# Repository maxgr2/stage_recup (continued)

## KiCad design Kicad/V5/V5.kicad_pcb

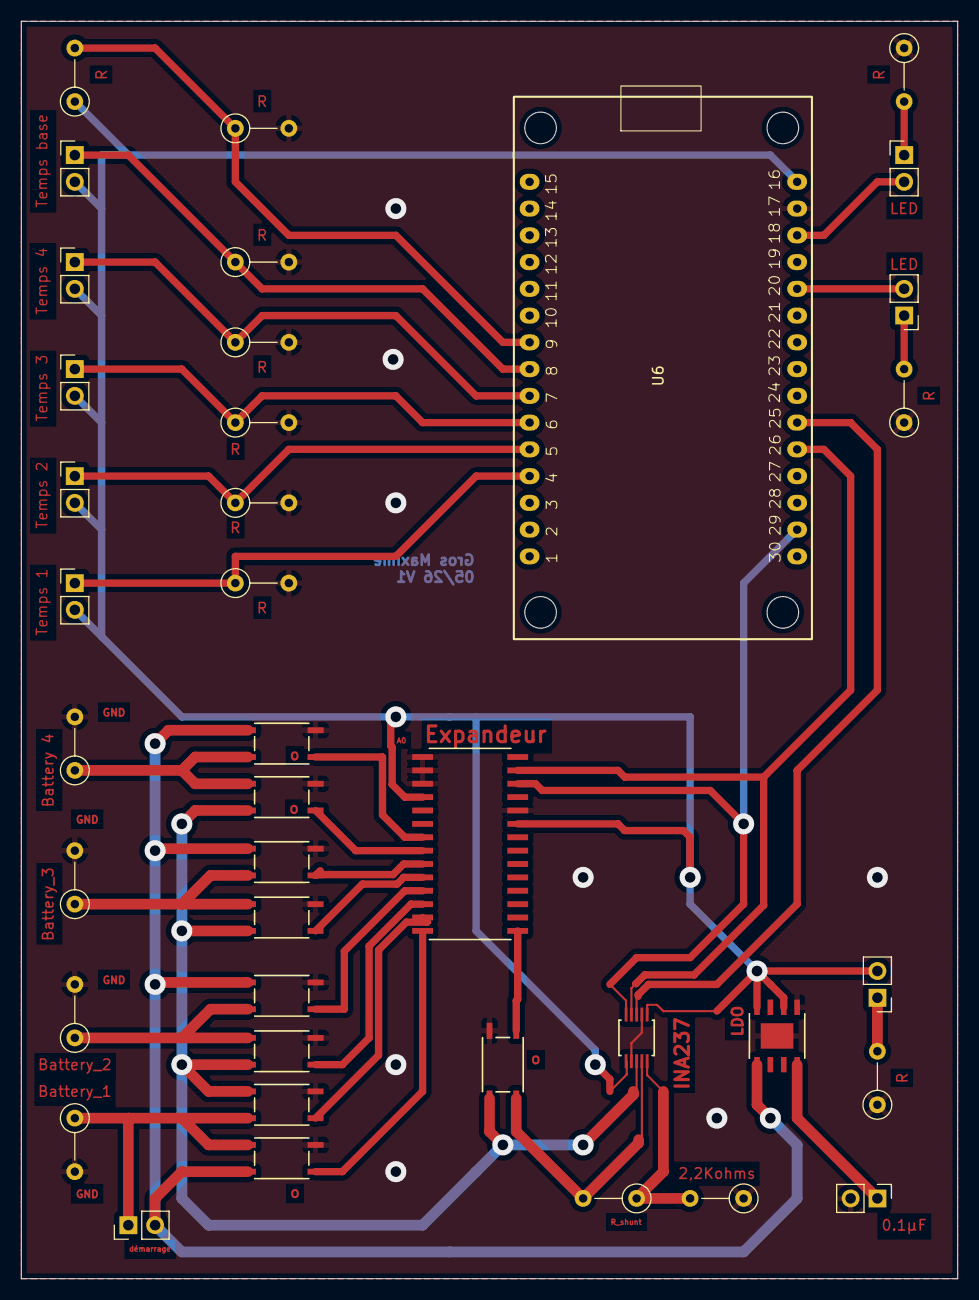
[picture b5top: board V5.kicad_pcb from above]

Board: 2 copper layers, 88.9 x 119.4 mm, 39 parts (0 on the bottom side), 34 nets.

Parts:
BT1: Battery_1; R_Axial_DIN0207_L6.3mm_D2.5mm_P5.08mm_Vertical
BT2: Battery_2; R_Axial_DIN0207_L6.3mm_D2.5mm_P5.08mm_Vertical
BT3: Battery_3; R_Axial_DIN0207_L6.3mm_D2.5mm_P5.08mm_Vertical
BT4: Battery 4; R_Axial_DIN0207_L6.3mm_D2.5mm_P5.08mm_Vertical
C1: 0.1µF; PinHeader_1x02_P2.54mm_Vertical
D1, D2, D3: LED; PinHeader_1x02_P2.54mm_Vertical
J1, J2, J3, J4, J5, J6: Conn_01x02_Pin; PinHeader_1x02_P2.54mm_Vertical
R1, R3, R4, R5, R6, R7, R8, R9, R10, R11, R12: R; R_Axial_DIN0207_L6.3mm_D2.5mm_P5.08mm_Vertical
R2: 2,2Kohms; R_Axial_DIN0207_L6.3mm_D2.5mm_P5.08mm_Vertical
U1, U2, U4, U8, U9, U10, U11, U12, U13: ISOM8600DFGR
U3: MCP23017-E/SO; MCP23017T-E&slash_SO
U5: MIC5283-3.3YME
U6: ESP32_30pin
U7: INA237AIDGSR

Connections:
+3.3V: D2.2 (A), J2.2, J3.2, J4.2, J5.2, J6.2, R5.1, U3.9 (VDD), U3.18 (*RESET), U5.6 (SNS), U5.8 (VOUT), U6.16 (3.3v), U7.1 (A1), U7.6 (VS)
CONT_ALIM1: U2.1 (AN), U3.28 (GPA7)
CONT_ALIM2: U3.25 (GPA4), U9.1 (AN)
CONT_ALIM3: U3.23 (GPA2), U11.1 (AN)
CONT_ALIM4: U3.21 (GPA0), U13.1 (AN)
CONT_MES1: U1.1 (AN), U3.27 (GPA6)
CONT_MES2: U3.26 (GPA5), U8.1 (AN)
CONT_MES3: U3.24 (GPA3), U10.1 (AN)
CONT_MES4: U3.22 (GPA1), U12.1 (AN)
GND: BT1.2 (-), BT2.2 (-), BT3.2 (-), BT4.2 (-), C1.2, R1.1, R2.1, R4.1, R6.2, R7.2, R8.2, R9.2, R10.2, R11.1, R12.2, U1.2 (CAT), U2.2 (CAT), U3.10 (VSS), U3.15 (A0), U3.16 (A1), U3.17 (A2), U4.2 (CAT), U5.5 (GND), U6.17 (GND), U7.2 (A0), U7.7 (GND), U8.2 (CAT), U9.2 (CAT), U10.2 (CAT), U11.2 (CAT), U12.2 (CAT), U13.2 (CAT)
MES_TOT: U3.1 (GPB0), U4.1 (AN)
unnamed: BT1.1 (+), J1.1, U1.4 (S1), U2.3 (S2)
unnamed: BT2.1 (+), U8.3 (S2), U9.4 (S1)
unnamed: BT3.1 (+), U10.3 (S2), U11.4 (S1)
unnamed: BT4.1 (+), U12.3 (S2), U13.4 (S1)
unnamed: D1.2 (A), U6.20 (GPIO4)
unnamed: D1.1 (K), R1.2
unnamed: D2.1 (K), R4.2
unnamed: D3.2 (A), U6.18 (GPIO15)
unnamed: D3.1 (K), R11.2
unnamed: R3.2, U4.4 (S1), U7.9 (IN-)
unnamed: C1.1, U5.4 (CPSRR)
unnamed: R2.2, R3.1, U7.10 (IN+)
SCL: U3.12 (SCL), U6.29 (GPIO22), U7.5 (SCL)
SDA: U3.13 (SDA), U6.26 (GPIO21), U7.4 (SDA)
VIN_LDO: J1.2, U2.4 (S1), U5.1 (VIN), U9.3 (S2), U11.3 (S2), U13.3 (S2)
V_BUS: U1.3 (S2), U4.3 (S2), U7.8 (VBUS), U8.4 (S1), U10.4 (S1), U12.4 (S1)
alert_INA237: U6.25 (GPIO19), U7.3 (ALERT)
temp_1: J2.1, R7.1, U6.7 (GPIO26)
temp_2: J3.1, R8.1, U6.6 (GPIO27)
temp_3: J4.1, R9.1, U6.5 (GPIO14)
temp_4: J5.1, R10.1, U6.4 (GPIO12)
temp_5: J6.1, R12.1, U6.8 (GPIO25)
temp_base: R5.2, R6.1, U6.9 (GPIO33)

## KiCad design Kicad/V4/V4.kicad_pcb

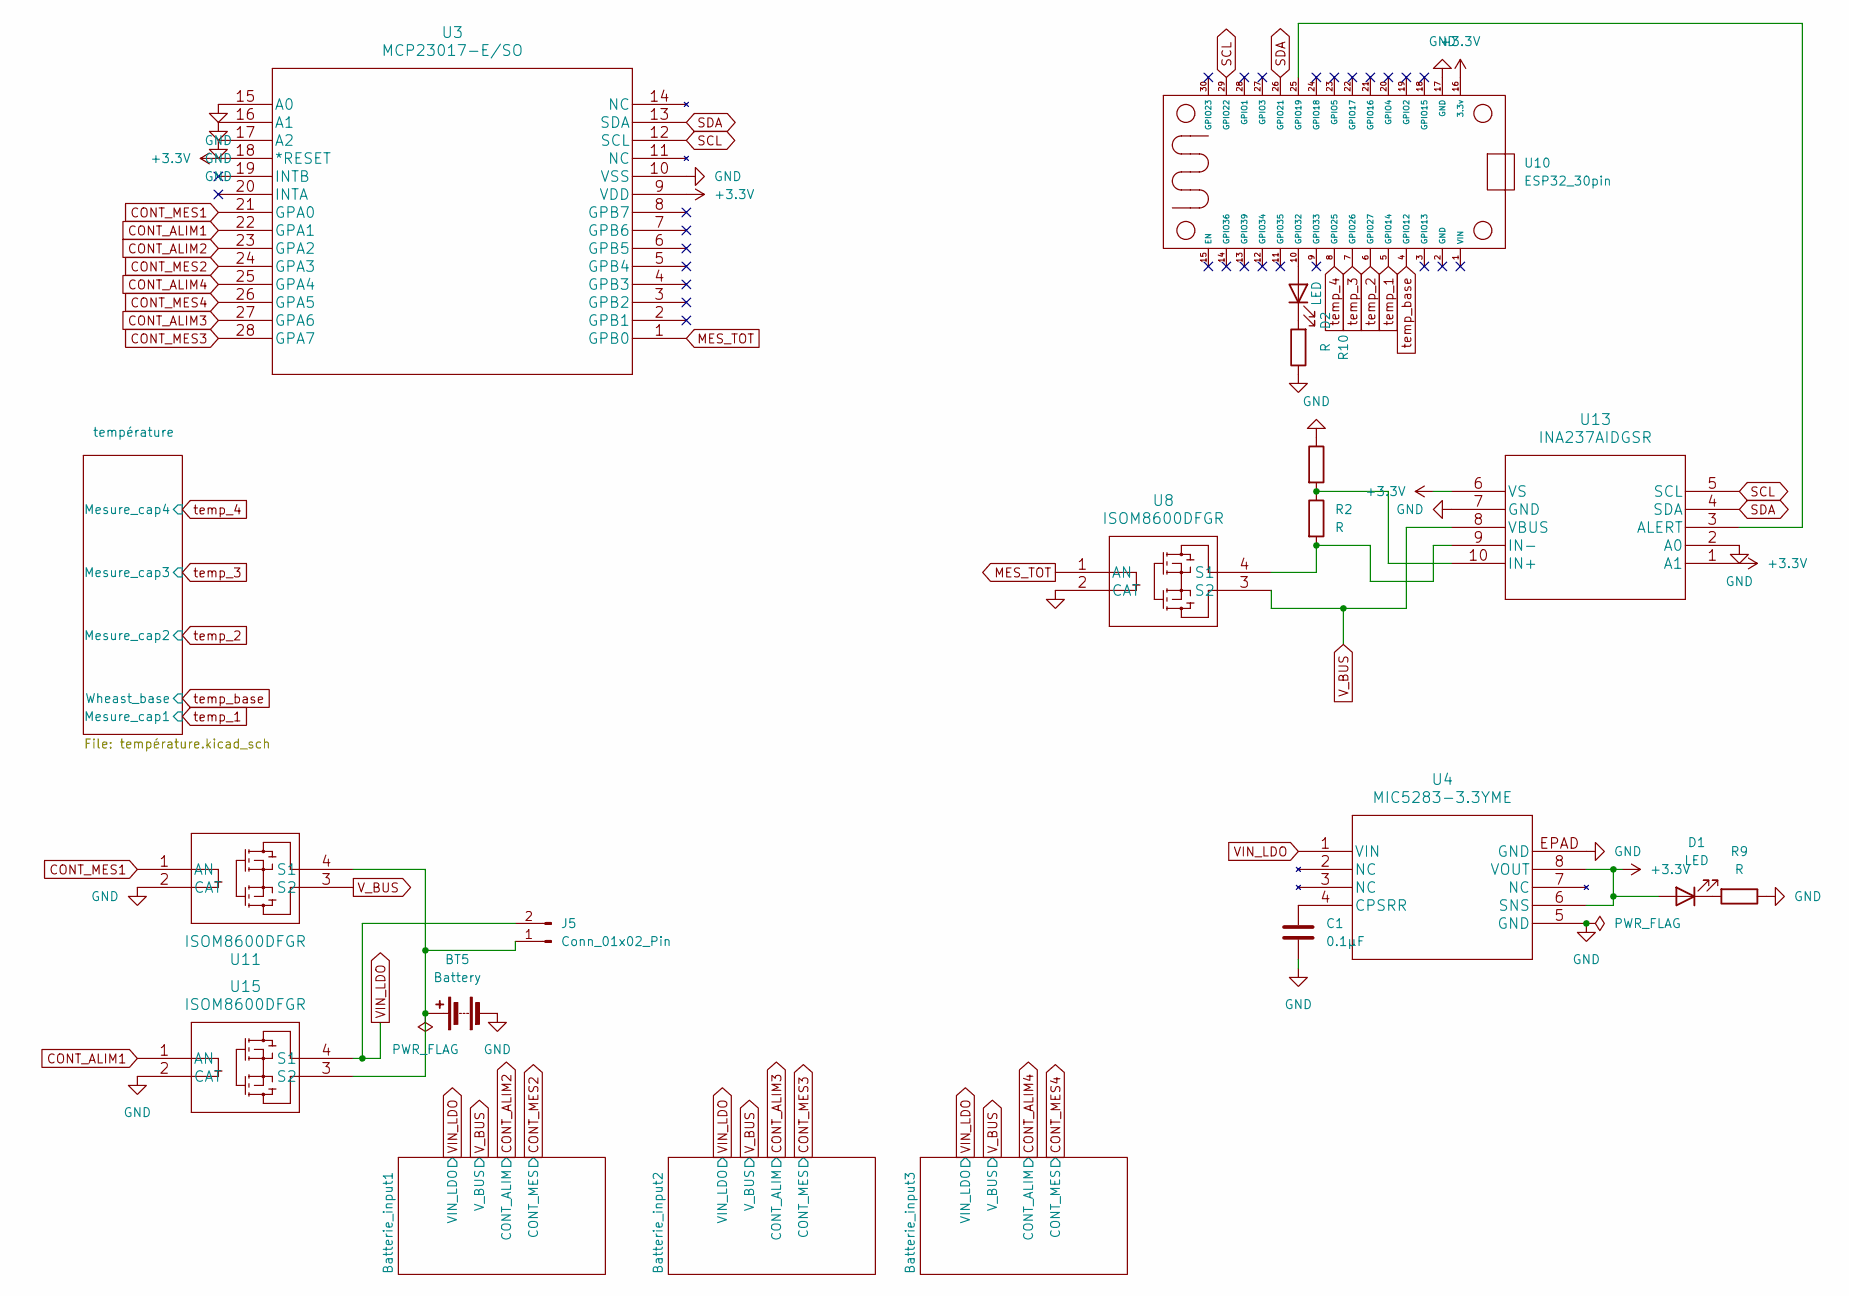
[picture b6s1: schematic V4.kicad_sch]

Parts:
BT5: Battery; PinHeader_1x02_P2.54mm_Vertical
C1: 0.1µF; PinHeader_1x02_P2.54mm_Vertical
D1, D2: LED; PinHeader_1x02_P2.54mm_Vertical
J5: Conn_01x02_Pin; PinHeader_1x02_P2.54mm_Vertical
R1: 2,2Kohms; R_Axial_DIN0207_L6.3mm_D2.5mm_P5.08mm_Vertical
R2, R9, R10: R; R_Axial_DIN0207_L6.3mm_D2.5mm_P5.08mm_Vertical
U3: MCP23017-E/SO; MCP23017T-E&slash_SO
U4: MIC5283-3.3YME
U8, U11, U15: ISOM8600DFGR
U10: ESP32_30pin
U13: INA237AIDGSR

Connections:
+3.3V: D1.2 (A), U3.9 (VDD), U3.18 (*RESET), U4.6 (SNS), U4.8 (VOUT), U10.16 (3.3v), U13.1 (A1), U13.6 (VS); also elsewhere on the board
CONT_ALIM1: U3.22 (GPA1), U15.1 (AN)
CONT_ALIM2: U3.23 (GPA2); also elsewhere on the board
CONT_ALIM3: U3.27 (GPA6); also elsewhere on the board
CONT_ALIM4: U3.25 (GPA4); also elsewhere on the board
CONT_MES1: U3.21 (GPA0), U11.1 (AN)
CONT_MES2: U3.24 (GPA3); also elsewhere on the board
CONT_MES3: U3.28 (GPA7); also elsewhere on the board
CONT_MES4: U3.26 (GPA5); also elsewhere on the board
GND: BT5.2 (-), C1.2, R1.1, R9.1, R10.1, U3.10 (VSS), U3.15 (A0), U3.16 (A1), U3.17 (A2), U4.5 (GND), U4.EPAD (GND), U8.2 (CAT), U10.17 (GND), U11.2 (CAT), U13.2 (A0), U13.7 (GND), U15.2 (CAT); also elsewhere on the board
MES_TOT: U3.1 (GPB0), U8.1 (AN)
unnamed: BT5.1 (+), J5.1, U11.4 (S1), U15.3 (S2)
unnamed: D1.1 (K), R9.2
unnamed: D2.2 (A), U10.10 (GPIO32)
unnamed: D2.1 (K), R10.2
unnamed: C1.1, U4.4 (CPSRR)
unnamed: U10.25 (GPIO19), U13.3 (ALERT)
unnamed: R1.2, R2.1, U13.10 (IN+)
unnamed: R2.2, U8.4 (S1), U13.9 (IN-)
SCL: U3.12 (SCL), U10.29 (GPIO22), U13.5 (SCL)
SDA: U3.13 (SDA), U10.26 (GPIO21), U13.4 (SDA)
VIN_LDO: J5.2, U4.1 (VIN), U15.4 (S1); also elsewhere on the board
V_BUS: U8.3 (S2), U11.3 (S2), U13.8 (VBUS); also elsewhere on the board
temp_1: U10.5 (GPIO14); also elsewhere on the board
temp_2: U10.6 (GPIO27); also elsewhere on the board
temp_3: U10.7 (GPIO26); also elsewhere on the board
temp_4: U10.8 (GPIO25); also elsewhere on the board
temp_base: U10.4 (GPIO12); also elsewhere on the board

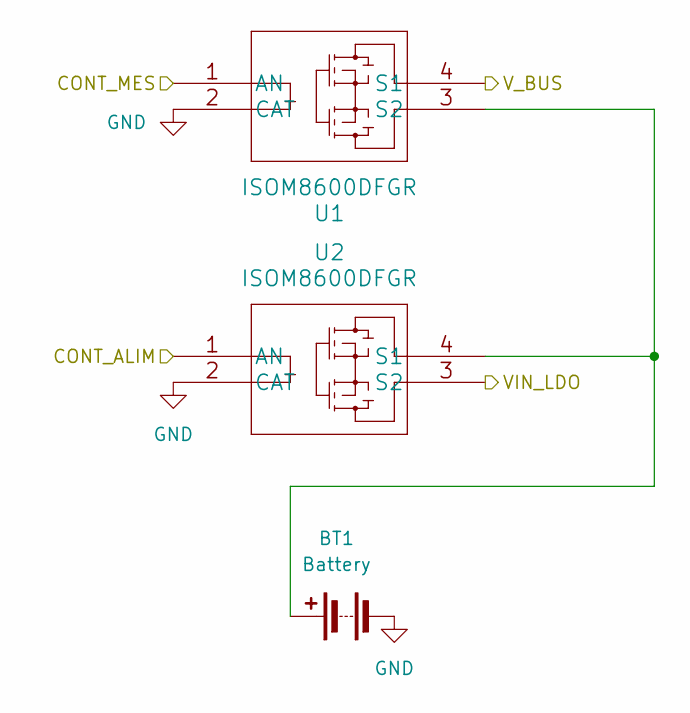
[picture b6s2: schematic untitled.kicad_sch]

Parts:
BT1: Battery; R_Axial_DIN0207_L6.3mm_D2.5mm_P5.08mm_Vertical
U1, U2: ISOM8600DFGR

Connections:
CONT_ALIM2: U2.1 (AN); also elsewhere on the board
CONT_MES2: U1.1 (AN); also elsewhere on the board
GND: BT1.2 (-), U1.2 (CAT), U2.2 (CAT); also elsewhere on the board
unnamed: BT1.1 (+), U1.3 (S2), U2.4 (S1)
VIN_LDO: U2.3 (S2); also elsewhere on the board
V_BUS: U1.4 (S1); also elsewhere on the board

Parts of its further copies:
BT3, BT4: Battery; R_Axial_DIN0207_L6.3mm_D2.5mm_P5.08mm_Vertical
U5, U6, U7, U9: ISOM8600DFGR

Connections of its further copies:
CONT_ALIM3: U6.1 (AN); also elsewhere on the board
CONT_ALIM4: U9.1 (AN); also elsewhere on the board
CONT_MES3: U5.1 (AN); also elsewhere on the board
CONT_MES4: U7.1 (AN); also elsewhere on the board
GND: BT3.2 (-), BT4.2 (-), U5.2 (CAT), U6.2 (CAT), U7.2 (CAT), U9.2 (CAT); also elsewhere on the board
unnamed: BT3.1 (+), U7.3 (S2), U9.4 (S1)
unnamed: BT4.1 (+), U5.3 (S2), U6.4 (S1)
VIN_LDO: U6.3 (S2), U9.3 (S2); also elsewhere on the board
V_BUS: U5.4 (S1), U7.4 (S1); also elsewhere on the board

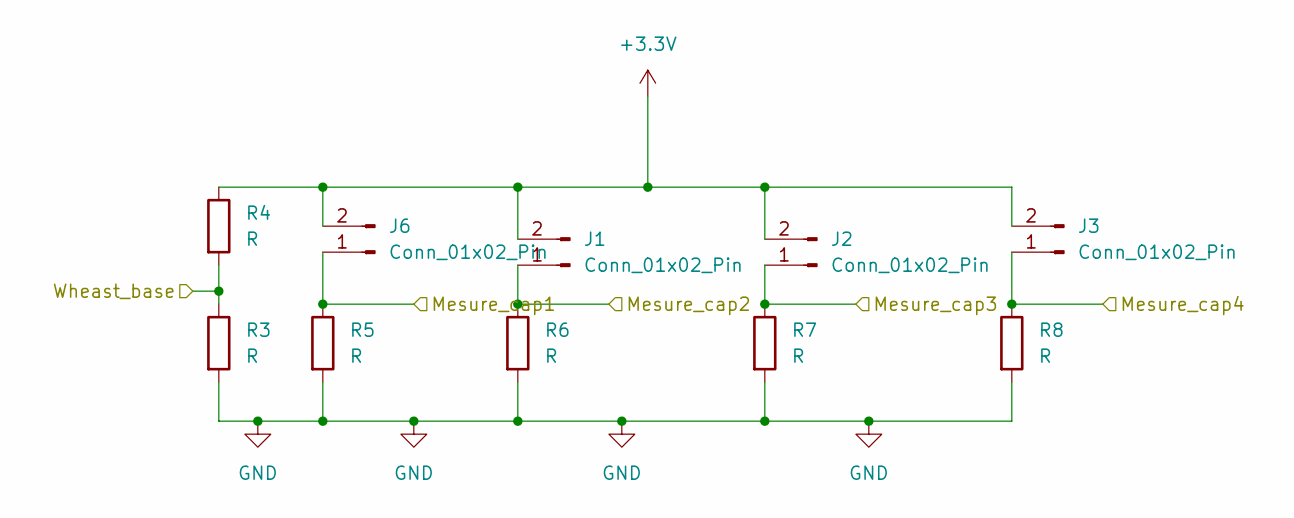
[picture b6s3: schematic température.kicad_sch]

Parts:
J1, J2, J3, J6: Conn_01x02_Pin; PinHeader_1x02_P2.54mm_Vertical
R3, R4, R5, R6, R7, R8: R; R_Axial_DIN0207_L6.3mm_D2.5mm_P5.08mm_Vertical

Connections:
+3.3V: J1.2, J2.2, J3.2, J6.2, R4.1; also elsewhere on the board
GND: R3.2, R5.2, R6.2, R7.2, R8.2; also elsewhere on the board
temp_1: J6.1, R5.1; also elsewhere on the board
temp_2: J1.1, R6.1; also elsewhere on the board
temp_3: J2.1, R7.1; also elsewhere on the board
temp_4: J3.1, R8.1; also elsewhere on the board
temp_base: R3.1, R4.2; also elsewhere on the board

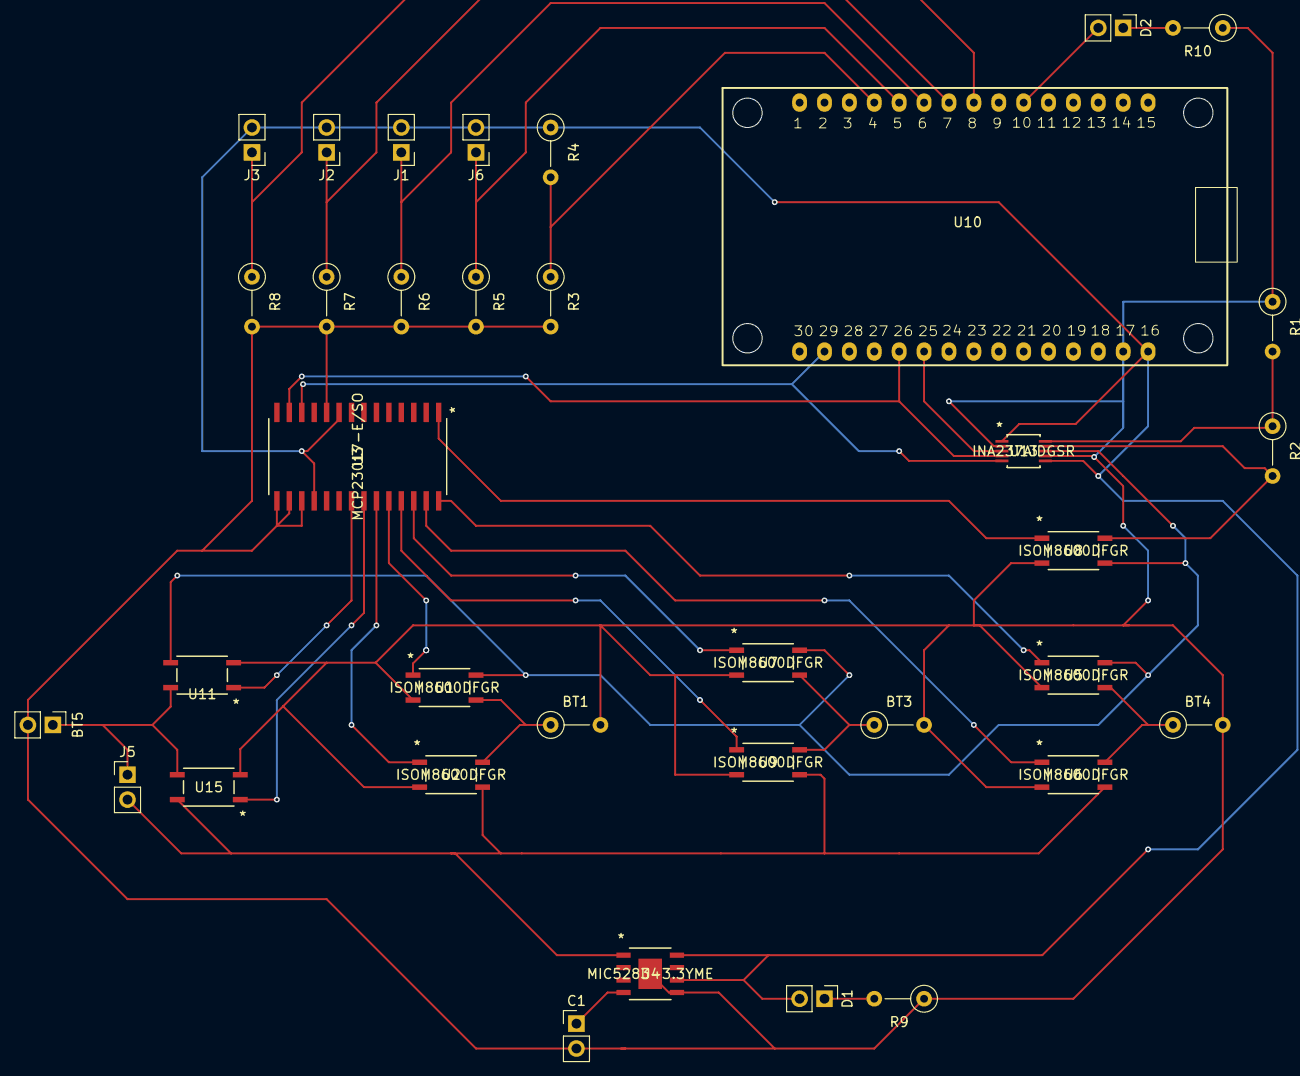
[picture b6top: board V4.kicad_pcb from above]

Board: 2 copper layers, 35 parts (0 on the bottom side), 31 nets.

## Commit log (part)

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2026-04-14 Initial commit: PlatformIO BLE battery monitor project
2026-04-15 essaie pour upload
2026-04-16 peux generer un sinus, c'est encore à tester
2026-04-16 a continuer à developper
2026-04-17 Prçets à tester mais pas de retour serial
2026-04-17 pres a tester
2026-04-20 le sinus fonctionne c'est testé
2026-04-20 sinus fonctionne testé
2026-04-20 ne marche pas complétement
2026-05-04 pcb_terminé
2026-05-04 I2C config en cours
2026-05-05 toutes les fonctions I2C écrite, il faut écrire les fonctions de gestion pure (batterie par batterie)
2026-05-06 ESP32 brownout à cause du bluetooth init
2026-05-06 premier essaie pas concluant
2026-05-07 version avec vrai température + création d'un fichier Json et enregistrement des donnée dedans
2026-05-11 affichage propre coté serveur, et mulitifhier pour plus de clarté
2026-05-11 affichage propore plusieurs fichier, a faire: ajouter la possiblité de mettre un nom au esp
2026-05-13 Modifs, 4 capteur, mesure de toute les batteries. mise en place d'un deep sleep
2026-05-21 ajout du projet salle blanche et pcb capteur fini
2026-05-22 modif de fin de semaine début du code pour le projet salle blanche
2026-06-05 4 pcb terminé
2026-06-09 fonction I2C SPS30
2026-06-09 Refactor I2C communication and add DFRobot RGB LCD support
    - Updated I2C.h to define SHT40 and SPS30 sensor communication methods.
    - Introduced SHT40 class for temperature and humidity readings.
    - Added SPS30 class for particulate matter measurements.
    - Created ecran.h and ecran.cpp for DFRobot RGB LCD1602 display handling.
    - Simplified main.cpp by removing unused DHT sensor references and integrating new display functionality.
2026-06-11 Essaie 1 jusqu'au SQL
2026-06-15 création des fonctions cartes filles mesure tensions
2026-06-25 Pojet batterie fonctionne, plus création du readme
